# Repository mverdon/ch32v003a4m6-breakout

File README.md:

# CH32V003A4M6 Breakout Board

This is a simple breakout board for prototyping with the CH32V003 MCU.
It uses the SOP-16 variant (CH32V003A4M6) so that it can be easily hand
soldered.

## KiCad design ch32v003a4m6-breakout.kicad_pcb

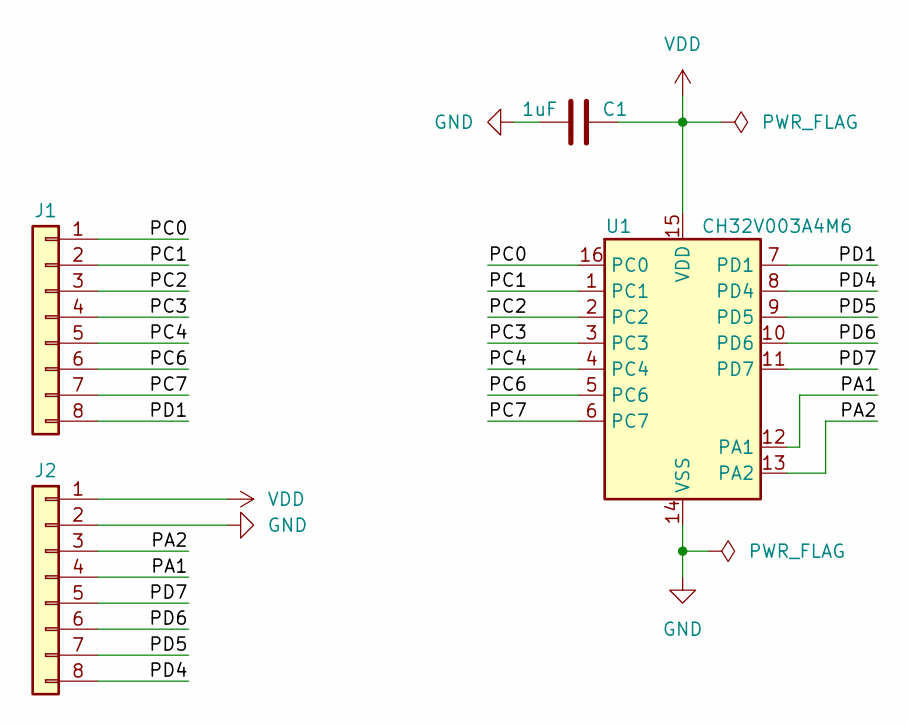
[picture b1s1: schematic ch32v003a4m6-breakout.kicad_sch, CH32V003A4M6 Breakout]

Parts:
C1: 1uF; C_0603_1608Metric
J1, J2: Conn_01x08; PinHeader_1x08_P2.54mm_Vertical
U1: CH32V003A4M6; SOP-16_3.9x9.9mm_P1.27mm

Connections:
/PA1: J2.4, U1.12 (PA1)
/PA2: J2.3, U1.13 (PA2)
/PC0: J1.1, U1.16 (PC0)
/PC1: J1.2, U1.1 (PC1)
/PC2: J1.3, U1.2 (PC2)
/PC3: J1.4, U1.3 (PC3)
/PC4: J1.5, U1.4 (PC4)
/PC6: J1.6, U1.5 (PC6)
/PC7: J1.7, U1.6 (PC7)
/PD1: J1.8, U1.7 (PD1)
/PD4: J2.8, U1.8 (PD4)
/PD5: J2.7, U1.9 (PD5)
/PD6: J2.6, U1.10 (PD6)
/PD7: J2.5, U1.11 (PD7)
GND: C1.1, J2.2, U1.14 (VSS)
VDD: C1.2, J2.1, U1.15 (VDD)

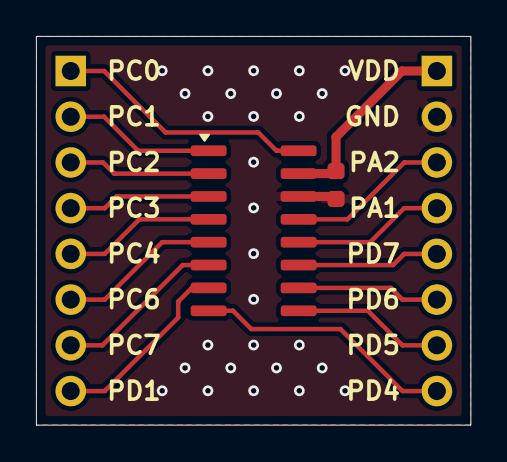
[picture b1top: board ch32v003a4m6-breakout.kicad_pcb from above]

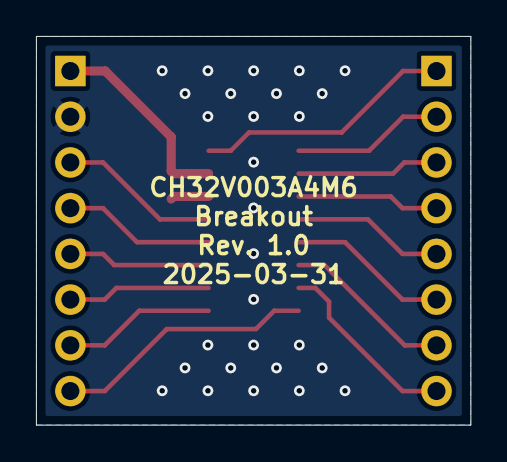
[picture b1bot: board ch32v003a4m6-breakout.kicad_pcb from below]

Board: 2 copper layers, 24.1 x 21.6 mm, 4 parts (2 on the bottom side), 16 nets.

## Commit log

2025-03-31 feat: add validation and build scripts
2025-04-06 fix: use default KiCad libraries
2025-04-06 fix: remove unused .gitmodules file
2025-04-06 feat(ci): add files for JLCPCB order
2025-04-06 feat(ci): add GitHub action workflow for building a board
